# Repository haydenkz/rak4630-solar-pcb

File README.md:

# rak4630-solar-pcb

Solar-powered MeshCore node PCB built around the **RAK4630-8-SM-I** (nRF52840 + SX1262 LoRa) module.

## Features
- RAK4630-8-SM-I LoRa / MCU module
- Dual-input Li-ion charging (USB-C and solar) via SGM41513 with power-path management
- SMT 18650 battery holder (MYOUNG BH-18650-B1BA002, LCSC C2988620) with NTC temperature sensing
- 3.3 V LDO rail (XC6206P332)
- Hardware low-voltage cutoff (MCP65R41 + TPS22917): switches the node off below ~3.30 V battery and back on above ~3.73 V; no firmware involvement. USB power always overrides it (D3), so the RAK can be flashed over USB with no cell or a flat one. JP1 bypasses it for bench use without USB or a cell.
- SWD programming / test points

## Files
| File | Description |
|------|-------------|
| `meshcore-solar.kicad_pro` | KiCad project |
| `meshcore-solar.kicad_sch` | Schematic |
| `meshcore-solar.kicad_pcb` | PCB layout |
| `meshcore-solar.pretty/`, `meshcore-solar.3dshapes/` | Project-local footprint (18650 holder) and 3D models |

## Requirements
- KiCad 10 (file format `generator_version 10.0`)
- Symbols and footprints are embedded in the design files. The battery holder footprint and 3D model live in the project library (`meshcore-solar.pretty`, `meshcore-solar.3dshapes`).

## Notes
- Solar panel connects to the PH2.0 `SOLAR IN` connector (P1) → SGM41513 `VAC`.
- No MPPT; the solar input feeds the charger's input-regulation loop directly.

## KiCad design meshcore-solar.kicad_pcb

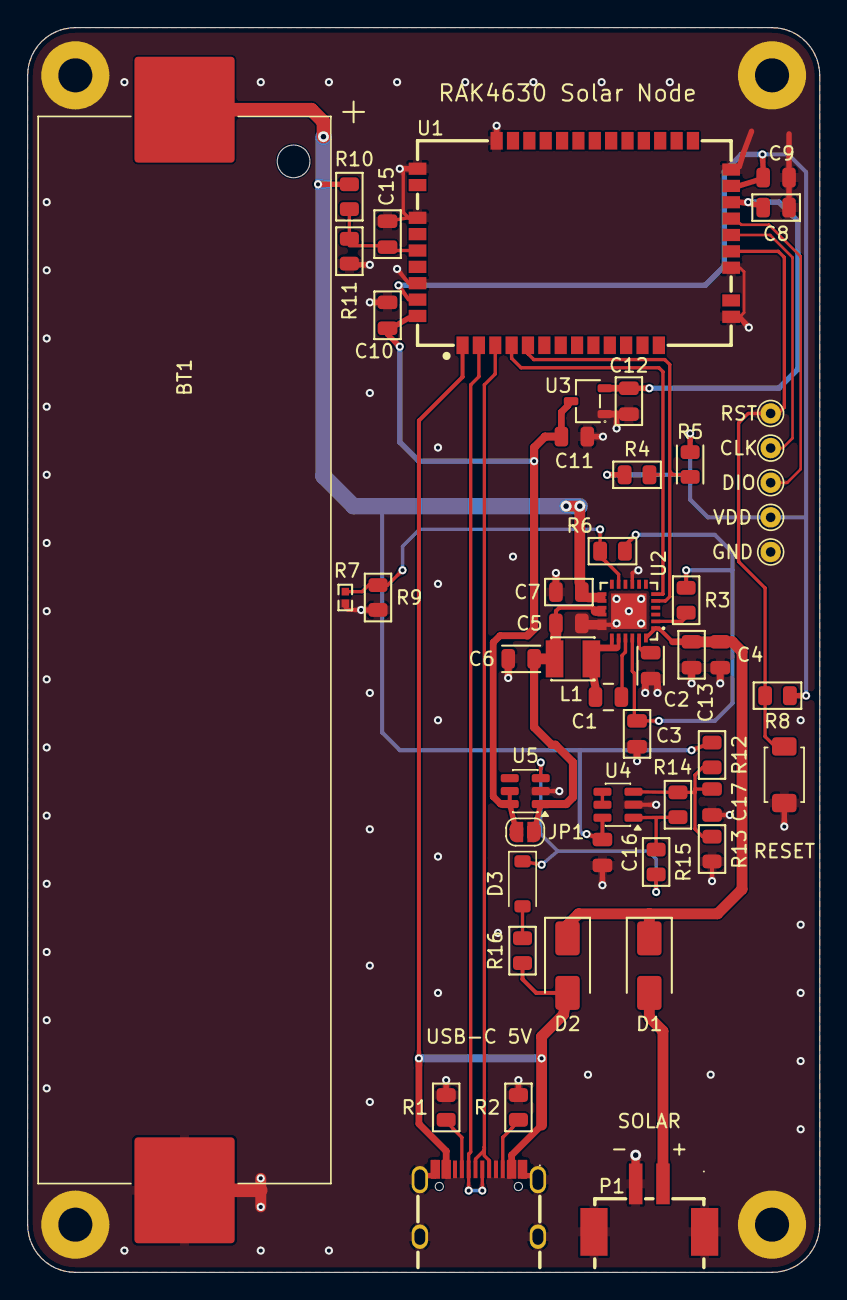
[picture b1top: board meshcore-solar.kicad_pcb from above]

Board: 2 copper layers, 58.1 x 91.3 mm, 55 parts (0 on the bottom side), 30 nets.

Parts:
BT1: BH-18650-B1BA002; BatteryHolder_MYOUNG_BH-18650-B1BA002_1x18650
C1: 47nF; C_0805
C2, C4, C5, C6, C7: 10uF; C_0805
C3, C12: 4.7uF; C_0805
C8, C9, C10, C15, C16, C17: 100nF; C_0805
C11, C13: 1uF; C_0805
D1, D2: SS34; D_SMA
D3: 1N4148W; D_SOD-123
H1, H2, H3, H4: MountingHole_2.5mm_Pad
JP1: Bypass; SolderJumper-2_P1.3mm_Open_RoundedPad1.0x1.5mm
L1: FNR3015S1R0MT; C167743_IND-SMD_L3_0-W3_0_FNR30XXS
P1: PH2.0-2P-LT; C722761_CONN-SMD_PH2_0-1X2PW
R1, R2, R6: 5.1kΩ; R_0805
R3: 2.2kΩ; R_0805
R4, R5, R8, R16: 10kΩ; R_0805
R7: NTCG103JF103FT1; C209959_R0402
R9: 27kΩ; R_0805
R10: 1MΩ; R_0805
R11: 1.5MΩ; R_0805
R12: 390kΩ; R_0805
R13: 200kΩ; R_0805
R14: 3MΩ; R_0805
R15: 100kΩ; R_0805
SW1: Tactile Button, 160gf; SW_TS-1088-AR02016
TP1: SWDIO; TestPoint_THTPad_D1.5mm_Drill0.7mm
TP2: SWDCLK; TestPoint_THTPad_D1.5mm_Drill0.7mm
TP3: NRF_RESET; TestPoint_THTPad_D1.5mm_Drill0.7mm
TP4: VDD_NRF; TestPoint_THTPad_D1.5mm_Drill0.7mm
TP5: GND; TestPoint_THTPad_D1.5mm_Drill0.7mm
U1: RAK4630-8-SM-I; C32315253_COMM-SMD_44P-L23_0-W15_0-P1_20_RAK4630-8-SM-I
U2: SGM41513YTQF24G/TR; C5153778_TQFN-24_L4_0-W4_0-P0_50-BL-EP2_6
U3: XC6206P332MR; SOT-23-3_L2.9-W1.6-P1.90-LS2.8-BR
U4: MCP65R41; SOT-23-6
U5: TPS22917; SOT-23-6
USBC1: TYPE-C-31-M-12; C165948_USB-C_SMD-TYPE-C-31-M-12_1

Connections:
+3V3: C8.1, C12.1, U1.20 (VBAT_SX), U3.2 (VOUT)
+BATT: BT1.1 (+), C7.1, C16.1, R10.1, R12.1, U2.13 (BAT), U2.14 (BAT), U4.6 (V+)
/CC1: R1.1, USBC1.A5 (CC1)
/CC2: R2.1, USBC1.B5 (CC2)
/CUTOFF_EN: R14.2, R15.1, U4.1
/NRF_RESET: R8.1, SW1.1, TP3.1, U1.17 (NRF_RESET)
/NTC: R6.1, R7.1, R9.2, U2.11 (TS)
/REGN: C3.1, R3.2, R6.2, U2.22 (REGN)
/SCL: R5.2, U1.5 (P0.14/12C_SCL), U2.5 (SCL)
/SDA: R4.2, U1.4 (P0.13/12C_SDA), U2.6 (SDA)
/SOL_VBUS: D1.2, P1.1
/SWDCLK: TP2.1, U1.18 (SWDCLK)
/SWDIO: TP1.1, U1.19 (SWDIO)
/SYS: C5.1, C6.1, JP1.1 (A), L1.2, U2.15 (SYS), U2.16 (SYS), U5.1 (VIN)
/SYS_SW: C10.1, C11.1, JP1.2 (B), U1.44 (VBAT_NRF), U3.3 (VIN), U5.5 (QOD), U5.6 (VOUT)
/USB+: U1.3 (USB+), USBC1.A6 (DP1), USBC1.B6 (DP2)
/USB-: U1.2 (USB-), USBC1.A7 (DN1), USBC1.B7 (DN2)
/VBAT_SENSE: C15.1, R10.2, R11.1, U1.40 (P0.05/AIN3)
/VBUS_IN: C4.1, C13.1, D1.1, D2.1, U2.1 (VAC), U2.24 (VBUS)
/VDD_NRF: C9.1, R4.1, R5.1, R8.2, TP4.1, U1.21 (VBAT_IO_SX), U1.43 (VDD_NRF)
GND: BT1.2 (-), C2.1, C3.2, C4.2, C5.2, C6.2, C7.2, C8.2, C9.2, C10.2, C11.2, C12.2, C13.2, C15.2, C16.2, C17.2, H1.1, H2.1, H3.1, H4.1, P1.2, P1.3, P1.4, R1.2, R2.2, R7.2, R9.1, R11.2, R13.2, SW1.2, TP5.1, U1.14 (GND), U1.16 (GND), U1.22 (GND), U1.35 (GND), U1.36 (GND), U1.38 (GND), U1.42 (GND), U2.9 (nCE), U2.17 (GND), U2.18 (GND), U2.25 (EP), U3.1 (GND), U4.2 (V-), U5.2 (GND), USBC1.1 (EH), USBC1.2 (EH), USBC1.3 (EH), USBC1.4 (EH), USBC1.A1B12 (GND), USBC1.B1A12 (GND)
unnamed: C1.2, L1.1, U2.19 (SW), U2.20 (SW)
unnamed: D3.2 (A), R16.2
unnamed: D3.1 (K), R15.2, U5.3 (ON)
unnamed: C1.1, U2.21 (BTST)
unnamed: C2.2, U2.23 (PMID)
unnamed: R3.1, U2.2 (PSEL)
unnamed: C17.1, R12.2, R13.1, R14.1, U4.3 (+)
unnamed: U4.4 (-), U4.5 (Vref)
VBUS: D2.2, R16.1, U1.1 (VBUS), USBC1.A4B9 (VBUS), USBC1.B4A9 (VBUS)
